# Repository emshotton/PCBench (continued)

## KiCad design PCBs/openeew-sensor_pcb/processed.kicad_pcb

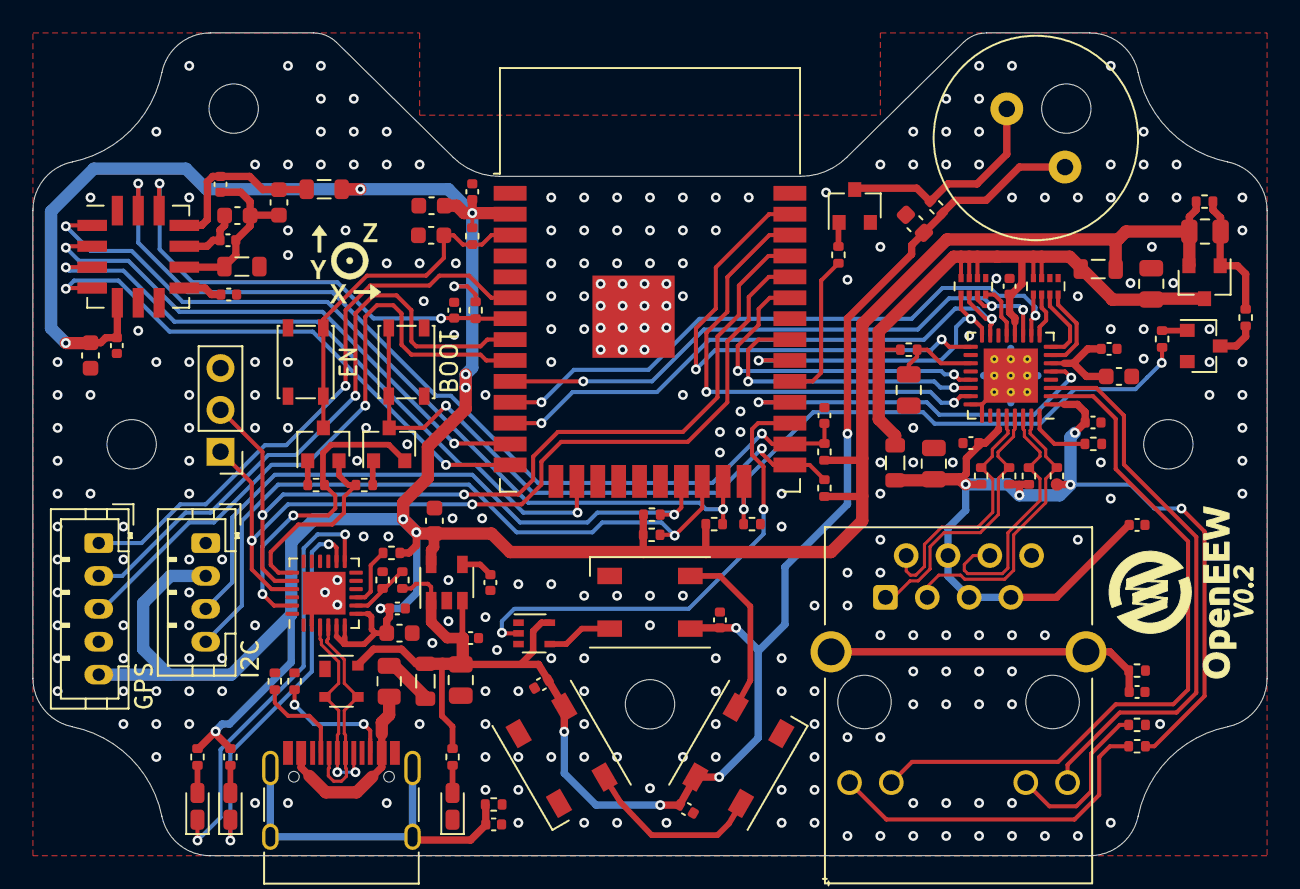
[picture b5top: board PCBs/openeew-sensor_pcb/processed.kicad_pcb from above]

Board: 2 copper layers, 75.0 x 50.0 mm, 101 parts (0 on the bottom side), 79 nets.

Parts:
BZ1: Piezo Buzzer; Buzzer_12.2x6.5mm
C1, C4, C17: 22uF; C_0805_2012Metric
C2, C9: 10uF; C_0805_2012Metric
C3, C13, C18, C30: 1uF; C_0603_1608Metric
C5, C6, C8, C10, C12, C14, C15, C16, C19, C20, C21, C22, C23, C24, C26, C32, C33: 100nF; C_0402_1005Metric
C7, C25, C28: 10uF; C_0603_1608Metric
C11: 2.2uF; C_0603_1608Metric
C27: 4.7uF; C_0603_1608Metric
C29, C31: 4.7nF; C_0402_1005Metric
C34: 470pF; C_0402_1005Metric
D1, D2, D3: WS2812B; LED_WS2812B_PLCC4_5.0x5.0mm_P3.2mm
D4: PRTR5V0U2X; SOT-143
D5, D6, D7: DNP; LED_0603_1608Metric_Castellated
F1: Polyfuse; Fuse_0805_2012Metric
FB1, FB2, FB3: MPZ2012S601ATD25; L_0805_2012Metric
J1: I2C; JST_PH_B4B-PH-K_1x04_P2.00mm_Vertical
J2: HR911105A; RJ45_Hanrun_HR911105A
J3: USB_C_Receptacle_USB2.0; USB_C_Receptacle_HRO_TYPE-C-31-M-12
J4: GPS; JST_PH_B5B-PH-K_1x05_P2.00mm_Vertical
J5: DNP; PinHeader_1x03_P2.54mm_Vertical
L1: DNP; L_0805_2012Metric
L2: MPZ2012S601ATD25; L_0805_2012Metric
Q1, Q3, Q4, Q5: BC817; SOT-23
Q2: WPM2015-3_TR; SOT-23
R1, R3, R5, R6, R12, R15, R23, R24, R25, R27, R29, R30: 10k; R_0402_1005Metric
R2, R13, R31, R32, R101, R102: 1k; R_0402_1005Metric
R7: 12.1k; R_0402_1005Metric
R8, R9, R10, R11: 49.9k; R_0402_1005Metric
R14: 510; R_0402_1005Metric
R16, R17: 5.11k; R_0402_1005Metric
R18: 22.1k; R_0402_1005Metric
R19: 47.5k; R_0402_1005Metric
R20, R21, R26: DNP; R_0402_1005Metric
R22, R28: 1M; R_0402_1005Metric
RN1, RN2: 2.2k; R_Array_Concave_4x0402
SW1, SW2: DNP; SW_SPST_PTS810
U1: ESP32-WROOM-32D; ESP32-WROOM-32
U2: LAN8710A; QFN-32-1EP_5x5mm_P0.5mm_EP3.3x3.3mm_ThermalVias
U3: ADXL355; PLCC-14
U4: MIC5219-3.3YM5; SOT-23-5
U5: 74LVC1G17; SOT-353_SC-70-5
U6: CP2102N-A01-GQFN24; QFN-24-1EP_4x4mm_P0.5mm_EP2.6x2.6mm

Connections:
3.3V_LAN: C4.1, C10.2, L1.2, L2.1, Q2.3, R5.1, RN1.3, RN1.4, RN2.2, RN2.3, RN2.4, U2.12
+3V3: C1.1, C7.2, C8.1, C13.1, C14.1, C25.1, C26.2, C27.2, FB2.2, J1.2, J4.5, L1.1, Q2.2, R1.1, R3.1, R6.1, R12.1, R15.1, R20.1, R21.1, R25.1, R29.1, R31.1, R32.1, U1.2, U3.5, U4.5, U6.5, U6.6, U6.7
+5V: BZ1.1, C2.2, C21.1, C22.1, C23.1, C24.2, C30.1, D1.1, D2.1, D3.1, D4.4, FB1.1, R14.1, R18.2, R26.1, U4.1, U4.3, U5.5
/ACCEL_VSS: C3.2, C5.2, C18.2, C33.2, FB3.2, U3.9
/ACCEL_VSUPPLY: C3.1, C5.1, FB2.1, U3.11
/AG1: J2.9, R102.2
/AY1: J2.12, U2.3
/BOOT: Q5.3, R6.2, SW2.1, U1.25
/BUZZ: R13.2, U1.29
/BZ-: BZ1.2, Q3.3, R14.2
/CC1: J3.A5, R17.1
/CC2: J3.B5, R16.1
/D5_K: D5.2, R20.2
/D6_K: D6.2, R21.2
/EMAC_CLKO_180: U1.28, U2.5
/EMAC_RXD0(RMII): RN2.7, U1.10, U2.11
/EMAC_RXD1(RMII): RN1.5, U1.11, U2.10
/EMAC_RX_CRS_DV: RN2.6, U1.12, U2.15
/EMAC_TXD0(RMII): U1.31, U2.22
/EMAC_TXD1(RMII): U1.36, U2.23
/EMAC_TX_EN(RMII): U1.33, U2.21
/EN: C28.2, Q4.3, R3.2, SW1.2, U1.3
/GPS_PPS: J4.1, U1.6
/GPS_RXD: J4.2, U1.8
/GPS_TXD: J4.3, U1.9
/H_CLK: U1.13, U3.2
/H_CS: R25.2, U1.23, U3.1
/H_MISO: U1.14, U3.4
/H_MOSI: U1.16, U3.3
/I2C_SCL: J1.4, R32.2, U1.22
/I2C_SDA: J1.3, R31.2, U1.21
/INT1: C20.1, R12.2, U1.7, U3.12
/INT2: C32.1, R29.2, U1.26, U3.13
/KG1: J2.10, U2.2
/KY1: J2.11, R101.1
/LAN_VDDCR: C11.2, C12.2, U2.6
/LAN_~RST: C9.2, R5.2, U2.19
/LDO_BYP: C34.1, U4.4
/LED_DAT0: D1.4, U5.4
/LED_DAT1: D1.2, D2.4
/LED_DAT2: D2.2, D3.4
/MDC(RMII): U1.37, U2.17
/MDIO(RMII): RN2.5, U1.30, U2.16
/NEOPIX_DI: U1.27, U5.2
/PHYAD0: RN2.8, U2.13
/PHYAD1: RN1.8, U2.7
/PHYAD2: RN1.7, U2.8
/PHY_PWR: R27.2, R30.2, U1.24
/PWR_LED: D7.2, R26.2
/Q1_C: Q1.3, R2.2
/Q2_G: C1.2, Q2.1, R1.2, R2.1
/Q3_B: Q3.1, R13.1
/Q4_B: Q4.1, R23.2
/Q5_B: Q5.1, R24.2
/RBIAS: R7.1, U2.32
/RJ_SH: C31.2, J2.SH, R28.1
/RMII_SEL: RN1.6, U2.9
/RXD0: J5.1, U1.34, U6.21
/RX_N: J2.6, R11.2, U2.30
/RX_P: J2.3, R10.2, U2.31
/TXD0: J5.2, U1.35, U6.20
/TX_N: J2.2, R9.2, U2.28
/TX_P: J2.1, R8.2, U2.29
/USB_D_N: D4.3, J3.A7, J3.B7, U6.4
/USB_D_P: D4.2, J3.A6, J3.B6, U6.3
/USB_SH: C29.2, J3.S1, R22.1
/V1P8ANA: C18.1, C33.1, U3.10
/V1P8DIG: C19.1, U3.8
/VBUS_C_F: F1.2, J3.A4, J3.A9, J3.B4, J3.B9
/VBUS_DETECT: R18.1, R19.1, U6.8
/VBUS_F_FB: F1.1, FB1.2
/VDD1_2A: C6.1, C15.2, C16.2, C17.2, J2.4, J2.5, J2.7, L2.2, R8.1, R9.1, R10.1, R11.1, R102.1, U2.1, U2.27
/~DTR: Q5.2, R23.1, U6.23
/~RST: R15.2, U6.9
/~RTS: Q4.2, R24.1, U6.19
/~RXT~_LED: D5.1, U6.13
/~TXT~_LED: D6.1, U6.14
GND: C2.1, C4.2, C6.2, C7.1, C8.2, C9.1, C10.1, C11.1, C12.1, C13.2, C14.2, C15.1, C16.1, C17.1, C19.2, C20.2, C21.2, C22.2, C23.2, C24.1, C25.2, C26.1, C27.1, C28.1, C29.1, C30.2, C31.1, C32.2, C34.2, D1.3, D2.3, D3.3, D4.1, D7.1, FB3.1, J1.1, J2.8, J3.A1, J3.A12, J3.B1, J3.B12, J4.4, J5.3, Q1.2, Q3.2, R7.2, R16.2, R17.2, R19.2, R22.2, R28.2, R30.1, R101.2, RN1.1, RN1.2, RN2.1, SW1.1, SW2.2, U1.1, U1.15, U1.38, U1.39, U2.24, U2.25, U2.33, U3.6, U4.2, U5.3, U6.2, U6.25
unnamed: Q1.1, R27.1

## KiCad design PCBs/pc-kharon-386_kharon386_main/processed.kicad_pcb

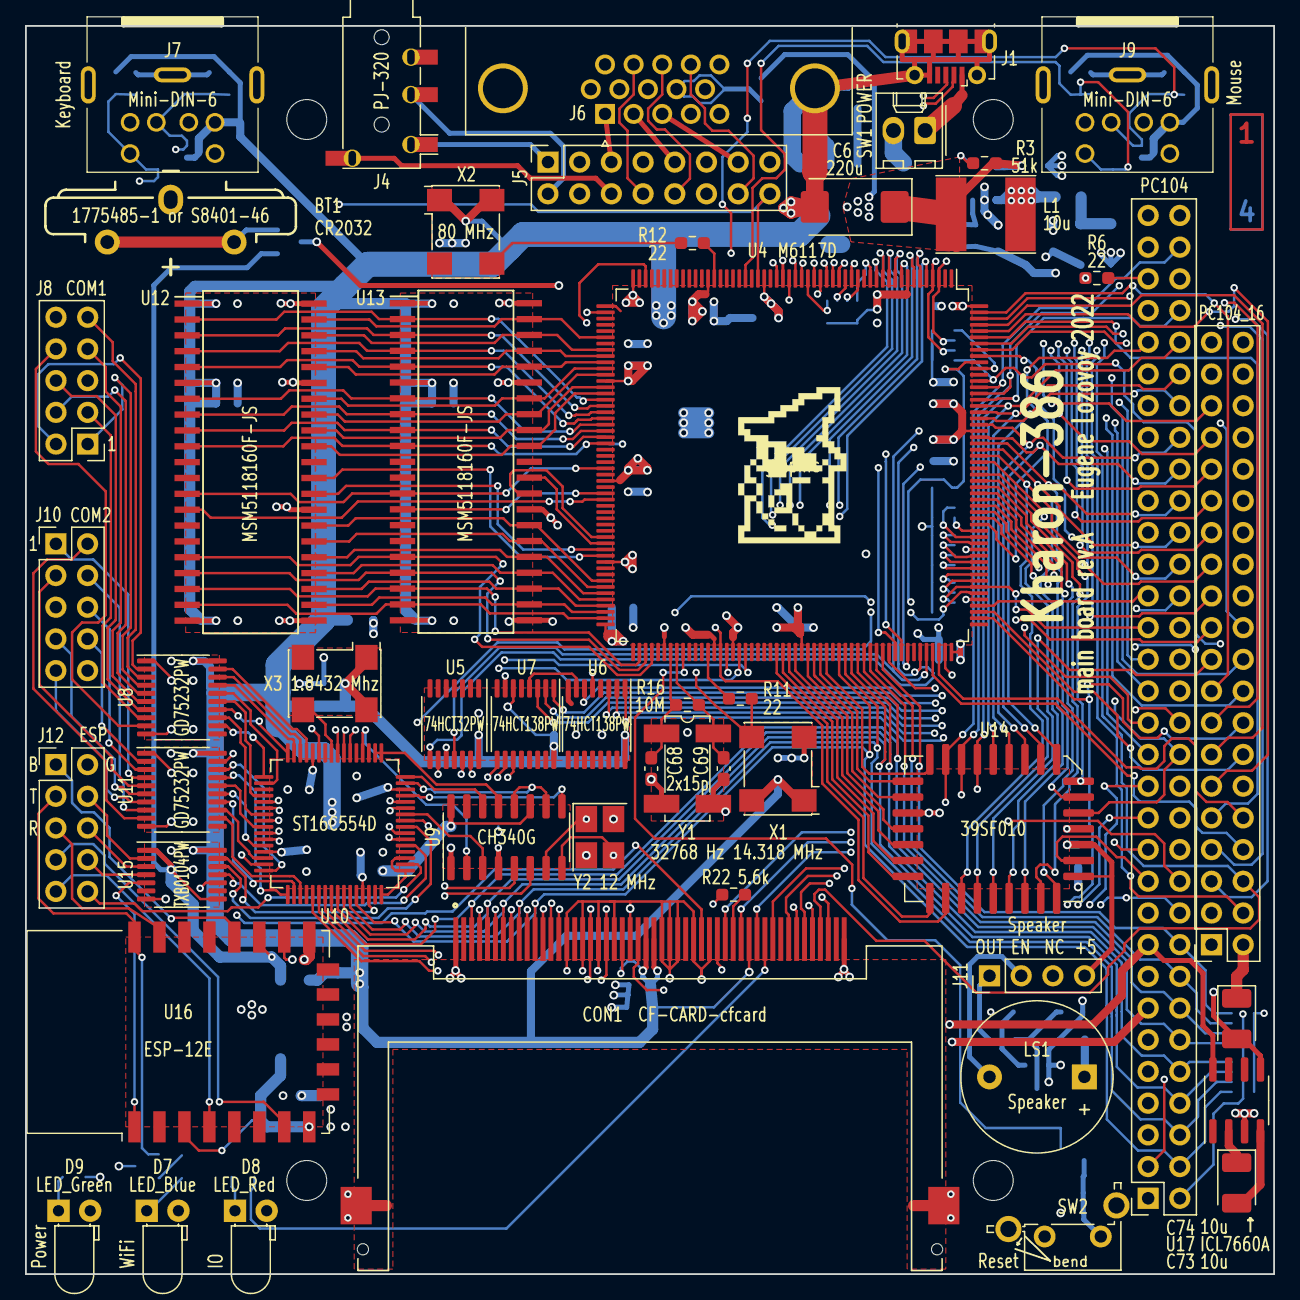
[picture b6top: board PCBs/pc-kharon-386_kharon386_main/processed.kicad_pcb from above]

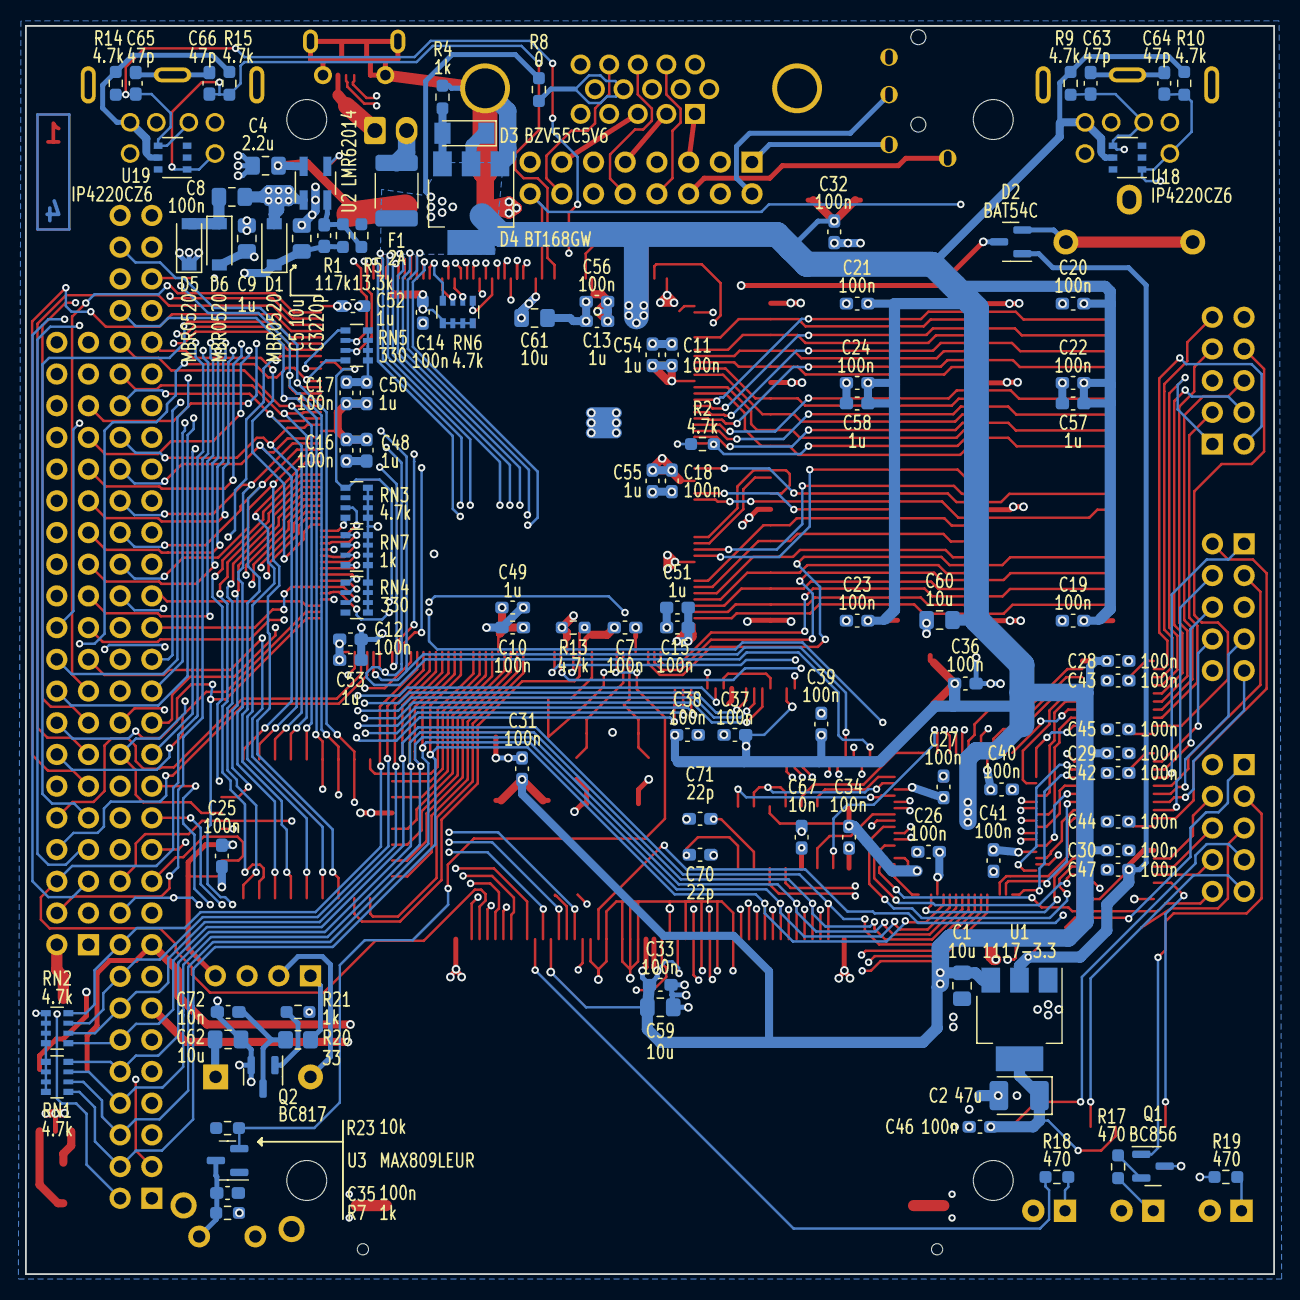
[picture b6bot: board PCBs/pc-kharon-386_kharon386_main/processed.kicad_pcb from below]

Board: 4 copper layers, 100.0 x 100.0 mm, 163 parts (107 on the bottom side), 248 nets.

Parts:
BT1: 1775485-1 or S8401-46; CR2032V
C1, C5, C59, C60, C61, C62: 10u; C_0805_2012Metric_Pad1.18x1.45mm_HandSolder
C2: 47u; CP_EIA-3528-21_Kemet-B_Pad1.50x2.35mm_HandSolder
C3: 220p; C_0603_1608Metric_Pad1.08x0.95mm_HandSolder
C4: 2.2u; C_0805_2012Metric_Pad1.18x1.45mm_HandSolder
C6: 220u; CP_EIA-7343-31_Kemet-D_Pad2.25x2.55mm_HandSolder
C7, C10, C11, C12, C13, C14, C15, C16, C17, C18, C19, C20, C21, C22, C23, C24, C25, C26, C27, C28, C29, C30, C31, C32, C33, C34, C35, C36, C37, C38, C39, C40, C41, C42, C43, C44, C45, C46, C47: 100n; C_0603_1608Metric_Pad1.08x0.95mm_HandSolder
C8: 100n; C_0805_2012Metric_Pad1.18x1.45mm_HandSolder
C9: 1u; C_0805_2012Metric_Pad1.18x1.45mm_HandSolder
C48, C49, C50, C51, C52, C53, C54, C55, C56, C57, C58: 1u; C_0603_1608Metric_Pad1.08x0.95mm_HandSolder
C63, C64, C65, C66: 47p; C_0603_1608Metric_Pad1.08x0.95mm_HandSolder
C67, C72: 10n; C_0603_1608Metric_Pad1.08x0.95mm_HandSolder
C68, C69: 15p; C_0603_1608Metric_Pad1.08x0.95mm_HandSolder
C70, C71: 22p; C_0603_1608Metric_Pad1.08x0.95mm_HandSolder
C73, C74: 10u; CP_EIA-3528-21_Kemet-B_Pad1.50x2.35mm_HandSolder
CON1: CF-CARD-cfcard; TE_1734451-1-LONG
D1, D5, D6: MBR0520; D_SOD-123
D2: BAT54C; SOT-23
D3: BZV55C5V6; D_MiniMELF
D4: BT168GW; SOT-223-3_TabPin2
D7: LED_Blue; LED_D3.0mm_Horizontal_O1.27mm_Z6.0mm
D8: LED_Red; LED_D3.0mm_Horizontal_O1.27mm_Z6.0mm
D9: LED_Green; LED_D3.0mm_Horizontal_O1.27mm_Z6.0mm
F1: 2A; Fuse_1812_4532Metric_Pad1.30x3.40mm_HandSolder
H1, H2, H3, H4: Screw M3 dk=5mm L=4mm; MountingHole_3.2mm_M3_dk5.2mm_Mask
J1: USB_B_Micro; USB_Micro-B_Molex-105017-0001
J2: PC104_16; PinSocket_2x20_P2.54mm_Vertical
J3: PC104; PinSocket_2x32_P2.54mm_Vertical
J4: PJ-320; PJ-320A_D
J5: Conn_02x08_Odd_Even; PinSocket_2x08_P2.54mm_Vertical
J6: DB15_Female_HighDensity_MountingHoles; DSUB-15-HD_Female_Horizontal_P2.29x1.98mm_EdgePinOffset3.03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
J7, J9: Mini-DIN-6; minidin-6
J8: COM1; PinHeader_2x05_P2.54mm_Vertical
J10: COM2; PinHeader_2x05_P2.54mm_Vertical
J11: Conn_01x04; PinHeader_1x04_P2.54mm_Vertical
J12: ESP; PinHeader_2x05_P2.54mm_Vertical
L1: 10u; L_Taiyo-Yuden_NR-60xx_HandSoldering
LOGO1: graphic; black-mage-12.5x8.6
LS1: Speaker; Buzzer_12x9.5RM7.6
Q1: BC856; SOT-23
Q2: BC817; SOT-23
R1: 117k; R_0603_1608Metric_Pad0.98x0.95mm_HandSolder
R2, R9, R10, R13, R14, R15: 4.7k; R_0603_1608Metric_Pad0.98x0.95mm_HandSolder
R3: 51k; R_0603_1608Metric_Pad0.98x0.95mm_HandSolder
R4, R7, R21: 1k; R_0603_1608Metric_Pad0.98x0.95mm_HandSolder
R5: 13.3k; R_0603_1608Metric_Pad0.98x0.95mm_HandSolder
R6, R11, R12: 22; R_0603_1608Metric_Pad0.98x0.95mm_HandSolder
R8: 0; R_0603_1608Metric_Pad0.98x0.95mm_HandSolder
R16: 10M; R_0603_1608Metric_Pad0.98x0.95mm_HandSolder
R17, R18, R19: 470; R_0603_1608Metric_Pad0.98x0.95mm_HandSolder
R20: 33; R_0805_2012Metric_Pad1.20x1.40mm_HandSolder
R22: 5.6k; R_0603_1608Metric_Pad0.98x0.95mm_HandSolder
R23: 10k; R_0603_1608Metric_Pad0.98x0.95mm_HandSolder
RN1, RN2, RN3, RN6: 4.7k; R_Array_Convex_4x0603
RN4, RN5: 330; R_Array_Convex_4x0603
RN7: 1k; R_Array_Convex_4x0603
SW1: Jumper / Pin header 1x2 Pitch=2.54mm; Molex_KK-254_AE-6410-02A_1x02_P2.54mm_Vertical
SW2: SW_Push; SW_Tactile_SPST_Angled_PTS645Vx83-2LFS
U1: 1117-3.3; SOT-223-3_TabPin2
U2: LMR62014; SOT-23-5_HandSoldering
U3: MAX809LEUR; SOT-23
U4: M6117D; PQFP-208_28x28mm_P0.5mm
U5: 74HCT32PW; TSSOP-14_4.4x5mm_P0.65mm
U6, U7: 74HCT138PW; TSSOP-16_4.4x5mm_P0.65mm
U8, U11: GD75232PW; TSSOP-20_4.4x6.5mm_P0.65mm
U9: CH340G; SOIC-16_3.9x9.9mm_P1.27mm
U10: ST16C554D; LQFP-64_10x10mm_P0.5mm
U12, U13: MSM5118160F-JS; SOJ-42
U14: 39SF010; PLCC-32_11.4x14.0mm_P1.27mm-longpads
U15: TXB0104PW; TSSOP-14_4.4x5mm_P0.65mm
U16: ESP-12E
U17: ICL7660A; SOIC-8_3.9x4.9mm_P1.27mm
U18, U19: IP4220CZ6; TSOP-6_1.65x3.05mm_P0.95mm
X1: 14.318 MHz; Oscillator_SMD_7050_7.0x5.0mm
X2: 80 MHz; Oscillator_SMD_7050_7.0x5.0mm
X3: 1.8432 Mhz; Oscillator_SMD_7050_7.0x5.0mm
Y1: 32768 Hz; Crystal_SMD_SeikoEpson_MC306-4Pin_8.0x3.2mm_HandSoldering
Y2: 12 MHz; Crystal_SMD_SeikoEpson_TSX3225-4Pin_3.2x2.5mm_HandSoldering

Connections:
+3V3: C2.1, C46.2, C47.2, D2.1, U1.2 (VO), U15.1 (VCCA), U15.8 (OE), U16.3 (EN), U16.8 (VCC), U16.17 (GPIO2)
+5V: C1.2, C4.2, C6.1, C10.2, C11.2, C12.2, C13.2, C14.2, C15.2, C16.2, C17.2, C18.2, C19.2, C20.2, C21.2, C22.2, C23.2, C24.2, C25.2, C26.2, C27.2, C28.2, C29.2, C30.2, C31.2, C32.2, C33.2, C34.1, C36.1, C37.1, C38.1, C39.1, C40.1, C41.1, C48.2, C49.2, C50.2, C51.2, C52.2, C53.2, C54.1, C55.1, C56.1, C57.1, C58.1, C59.1, C60.1, C61.1, C62.1, CON1.13 (VCC2), CON1.36 (~WE), CON1.38 (VCC1), CON1.44 (~REG), D3.1 (K), D4.2 (A), D7.2 (A), D8.2 (A), D9.2 (A), F1.1, J2.34, J3.5, J3.57, J7.4, J9.4, J11.4, L1.1, LS1.1, R2.1, R3.1, R7.1, R8.1, R9.1, R10.1, R14.1, R15.1, RN1.5 (R4.2), RN1.6 (R3.2), RN1.7 (R2.2), RN1.8 (R1.2), RN2.5 (R4.2), RN2.6 (R3.2), RN2.7 (R2.2), RN2.8 (R1.2), RN3.5 (R4.2), RN3.6 (R3.2), RN3.7 (R2.2), RN3.8 (R1.2), RN4.5 (R4.2), RN4.6 (R3.2), RN4.7 (R2.2), RN4.8 (R1.2), RN5.5 (R4.2), RN5.6 (R3.2), RN5.7 (R2.2), RN5.8 (R1.2), RN7.5 (R4.2), RN7.6 (R3.2), RN7.7 (R2.2), RN7.8 (R1.2), U1.3 (VI), U2.5 (Vin), U4.1 (VCC1), U4.15 (VCC2), U4.38 (VCC3), U4.46 (VCC4), U4.53 (VCC5), U4.59 (VCC6), U4.76 (VCC7), U4.85 (VCC8), U4.105 (VCC9), U4.125 (VCC11), U4.137 (VCC12), U4.150 (VCC13), U4.157 (VCC14), U4.182 (VCC15), U4.197 (VCC16), U5.14 (VCC), U6.16 (VCC), U7.6 (E3), U7.16 (VCC), U8.20 (VCC), U9.11 (~RI), U9.16 (VCC), U10.4 (VCC), U10.19 (RIB#), U10.21 (VCC), U10.35 (VCC), U10.52 (VCC), U10.63 (RIA#), U11.20 (VCC), U12.1 (VCC), U12.6 (VCC), U12.21 (VCC), U13.1 (VCC), U13.6 (VCC), U13.21 (VCC), U14.1 (A18), U14.30 (A17), U14.32 (VCC), U15.14 (VCCB), U18.5 (+), U19.5 (+), X1.1 (EN), X1.4 (V+), X2.1 (EN), X2.4 (V+), X3.1 (EN), X3.4 (V+)
+12V: C3.1, C5.2, C42.2, C43.2, D1.1 (K), J3.17, R1.1, U8.1 (VDD), U11.1 (VDD), U17.8 (V+)
+BATT: C7.1, D2.3, U4.110 (VBAT)
-12V: C9.1, C44.2, C45.2, C74.2, D6.2 (A), J3.13, U8.10 (VSS), U11.10 (VSS), U17.5 (VOUT)
/0x2E8: U7.11 (O4), U10.7 (CSA#)
/0x2F8: U7.9 (O6), U10.42 (CSD#)
/0x3E8: U7.10 (O5), U10.11 (CSB#)
/0x3F8: U7.7 (O7), U10.38 (CSC#)
/14MHz: R6.2, R11.2, X1.3 (OUT)
/AEN: J3.22, RN3.1 (R1.1), U4.199 (AEN), U6.5 (E2)
/BALE: J3.55, U4.173 (BALE)
/BD0: R2.2, U4.75 (BD0), U12.10 (DQ7), U13.10 (DQ7)
/BD1: U4.74 (BD1), U12.9 (DQ6), U13.9 (DQ6)
/BD2: U4.73 (BD2), U12.8 (DQ5), U13.8 (DQ5)
/BD3: U4.72 (BD3), U12.7 (DQ4), U13.7 (DQ4)
/BD4: U4.71 (BD4), U12.5 (DQ3), U13.5 (DQ3)
/BD5: U4.70 (BD5), U12.4 (DQ2), U13.4 (DQ2)
/BD6: U4.69 (BD6), U12.3 (DQ1), U13.3 (DQ1)
/BD7: U4.68 (BD7), U12.2 (DQ0), U13.2 (DQ0)
/BD8: U4.67 (BD8), U12.33 (DQ8), U13.33 (DQ8)
/BD9: U4.66 (BD9), U12.34 (DQ9), U13.34 (DQ9)
/BD10: U4.64 (BD10), U12.35 (DQ10), U13.35 (DQ10)
/BD11: U4.63 (BD11), U12.36 (DQ11), U13.36 (DQ11)
/BD12: U4.62 (BD12), U12.38 (DQ12), U13.38 (DQ12)
/BD13: U4.61 (BD13), U12.39 (DQ13), U13.39 (DQ13)
/BD14: U4.60 (BD14), U12.40 (DQ14), U13.40 (DQ14)
/BD15: U4.58 (BD15), U12.41 (DQ15), U13.41 (DQ15)
/CAS0J0: U4.93 (CAS0LJ), U12.31 (~LCAS)
/CAS0J1: U4.92 (CAS0HJ), U12.30 (~UCAS)
/CAS1J0: U4.91 (CAS1LJ), U13.31 (~LCAS)
/CAS1J1: U4.90 (CAS1HJ), U13.30 (~UCAS)
/CD_COM1: U8.17 (RY3), U10.31 (CDC#)
/CD_COM2: U10.49 (CDD#), U11.17 (RY3)
/CLK2: R12.2, X2.3 (OUT)
/CTS1: J8.8, U8.9 (RA5)
/CTS2: J10.8, U11.2 (RA1)
/CTS_COM1: U8.12 (RY5), U10.33 (CTSC#)
/CTS_COM2: U10.47 (CTSD#), U11.19 (RY1)
/CTS_ESP: J12.10, U10.2 (CTSA#)
/CTS_USB: U9.14 (~RTS), U10.16 (CTSB#)
/DACK0: J2.18, RN6.7 (R2.2), U4.16 (DACK0J)
/DACK1: J3.33, RN6.6 (R3.2), U4.18 (DACK1J)
/DACK2: J3.51, U4.20 (DACK2J)
/DACK3: J3.29, U4.22 (DACK3J)
/DACK5: J2.22, RN6.5 (R4.2), U4.24 (DACK5J)
/DACK6: J2.26, U4.26 (DACK6J)
/DACK7: J2.30, U4.28 (DACK7J)
/DCD1: J8.1, U8.4 (RA3)
/DCD2: J10.1, U11.4 (RA3)
/DRQ0: J2.20, U4.17 (DRQ0)
/DRQ1: J3.35, U4.19 (DRQ1)
/DRQ2: J3.11, U4.21 (DRQ2)
/DRQ3: J3.31, U4.23 (DRQ3)
/DRQ5: J2.24, U4.25 (DRQ5)
/DRQ6: J2.28, U4.27 (DRQ6)
/DRQ7: J2.32, U4.29 (DRQ7)
/DSR1: J8.6, U8.7 (RA4)
/DSR2: J10.6, U11.3 (RA2)
/DSR_COM1: U8.14 (RY4), U10.32 (DSRC#)
/DSR_COM2: U10.48 (DSRD#), U11.18 (RY2)
/DSR_USB: U9.13 (~DTR), U10.17 (DSRB#), U10.18 (CDB#)
/DTR1: J8.4, U8.5 (DY1)
/DTR2: J10.4, U11.8 (DY3)
/DTR_COM1: U8.16 (DA1), U10.34 (DTRC#)
/DTR_COM2: U10.46 (DTRD#), U11.13 (DA3)
/DTR_USB: U9.10 (~DSR), U9.12 (~DCD), U10.15 (DTRB#)
/ESP_BOOT: J12.1, U16.18 (GPIO0)
/ESP_CTS: J12.7, U16.7 (GPIO13)
/ESP_RST: U15.5 (A4), U16.1 (~RST)
/ESP_RTS: J12.9, U16.4 (GPIO16)
/ESP_RX: J12.5, U16.21 (GPIO3/RXD)
/ESP_TX: J12.3, Q1.1 (B), U16.22 (GPIO1/TXD)
/HDCS0: CON1.7 (~CS0), U4.50 (HDCS0J)
/HDCS1: CON1.32 (~CS1), U4.54 (HDCS1J)
/IOCHK: J3.2, RN5.4 (R4.1), U4.196 (IOCHKJ)
/IOCHRDY: CON1.42 (IORDY), J3.20, RN4.2 (R2.1), U4.164 (IOCHRDY)
/IOCS16: CON1.24 (~IOCS16), J2.6, RN5.2 (R2.1), U4.3 (IO16J)
/IOR: CON1.34 (~IORD), J3.27, RN7.4 (R4.1), U4.166 (IORJ), U10.40 (IOR#)
/IOW: CON1.35 (~IOWR), J3.25, RN7.3 (R3.1), U4.167 (IOWJ), U10.9 (IOW#)
/IRQ3: J3.49, U4.152 (IRQ3), U5.11
/IRQ4: J3.47, U4.151 (IRQ4), U5.8
/IRQ5: J3.45, U4.149 (IRQ5)
/IRQ6: J3.43, U4.148 (IRQ6)
/IRQ7: J3.41, U4.147 (IRQ7)
/IRQ9: J3.7, U4.146 (IRQ9)
/IRQ10: J2.8, U4.153 (IRQ10)
/IRQ11: J2.10, U4.154 (IRQ11)
/IRQ14: CON1.37 (INTRQ), J2.16, U4.158 (IRQ14)
/IRQ15: J2.14, U4.159 (IRQ15)
/KBCLK: C64.1, J7.5, R10.2, U4.122 (KBCLK), U18.1
/KBDAT: C63.1, J7.1, R9.2, U4.123 (KBDATA), U18.4
/KBSJ: R13.2, U4.119 (ROMKBCSJ), U14.22 (~CE)
/LA17: J2.17, U4.207 (LA17)
/LA18: J2.15, U4.206 (LA18)
/LA19: J2.13, U4.205 (LA19)
/LA20: J2.11, U4.204 (LA20)
/LA21: J2.9, U4.203 (LA21)
/LA22: J2.7, U4.202 (LA22)
/LA23: J2.5, U4.201 (LA23)
/MA0: U4.108 (MA0), U12.17 (MA0), U13.17 (MA0)
/MA1: U4.107 (MA1), U12.18 (MA1), U13.18 (MA1)
/MA2: U4.106 (MA2), U12.19 (MA2), U13.19 (MA2)
/MA3: U4.103 (MA3), U12.20 (MA3), U13.20 (MA3)
/MA4: U4.102 (MA4), U12.23 (MA4), U13.23 (MA4)
/MA5: U4.101 (MA5), U12.24 (MA5), U13.24 (MA5)
/MA6: U4.100 (MA6), U12.25 (MA6), U13.25 (MA6)
/MA7: U4.99 (MA7), U12.26 (MA7), U13.26 (MA7)
/MA8: U4.98 (MA8), U12.27 (MA8), U13.27 (MA8)
/MA9: U4.97 (MA9), U12.28 (MA9), U13.28 (MA9)
/MASTER: J2.36, RN5.1 (R1.1), U4.198 (MASTERJ)
/MEMCS16: J2.4, RN5.3 (R3.1), U4.4 (MEM16J)
/MEMR: J2.19, RN3.3 (R3.1), U4.171 (MRDJ), U14.24 (~OE)
/MEMW: J2.21, RN3.4 (R4.1), U4.172 (MWTJ)
/MSCLK: C66.1, J9.5, R15.2, U4.34 (MSCLK), U19.1
/MSDAT: C65.1, J9.1, R14.2, U4.155 (IRQ12/MSDATA), U19.4
/NOWS: J3.15, RN4.1 (R1.1), U4.165 (NOWSJ)
/PWG: R23.1, U3.2 (~RST), U4.113 (PWG)
/RASJ0: U4.84 (RAS0J), U12.14 (~RAS)
/RASJ1: U4.83 (RAS1J), U13.14 (~RAS)
/REFRESH: J3.37, RN4.3 (R3.1), U4.163 (REFRESHJ)
/RESETL: CON1.41 (~RESET), U4.120 (RESETLJ), U15.10 (B4)
/RI1: J8.9, U8.3 (RA2)
/RI2: J10.9, U11.7 (RA4)
/RI_COM1: U8.18 (RY2), U10.30 (RIC#)
/RI_COM2: U10.50 (RID#), U11.14 (RY4)
/RSTDRV: J3.3, U4.162 (RSTDRV), U10.27 (RESET)
/RTS1: J8.7, U8.6 (DY2)
/RTS2: J10.7, U11.6 (DY2)
/RTS_COM1: U8.15 (DA2), U10.36 (RTSC#)
/RTS_COM2: U10.44 (RTSD#), U11.15 (DA2)
/RTS_ESP: U10.5 (RTSA#), U15.11 (B3)
/RTS_USB: U9.9 (~CTS), U10.13 (RTSB#)
/RX1: J8.2, U8.2 (RA1)
/RX2: J10.2, U11.9 (RA5)
/RX_COM1: U8.19 (RY1), U10.29 (RXC)
/RX_COM2: U10.51 (RXD), U11.12 (RY5)
/RX_ESP: U10.62 (RXA), U15.13 (B1)
/RX_USB: U9.2 (TXD), U10.20 (RXB)
/SA0: CON1.20 (A0), J3.62, U4.195 (SA0), U10.24 (A0), U14.12 (A0)
/SA1: CON1.19 (A1), J3.60, U4.194 (SA1), U10.23 (A1), U14.11 (A1)
/SA2: CON1.18 (A2), J3.58, U4.193 (SA2), U10.22 (A2), U14.10 (A2)
/SA3: J3.56, U4.192 (SA3), U7.3 (A2), U14.9 (A3)
/SA4: J3.54, U4.191 (SA4), U7.2 (A1), U14.8 (A4)
/SA5: J3.52, U4.190 (SA5), U6.6 (E3), U14.7 (A5)
/SA6: J3.50, U4.189 (SA6), U6.1 (A0), U14.6 (A6)
/SA7: J3.48, U4.187 (SA7), U6.2 (A1), U14.5 (A7)
/SA8: J3.46, U4.186 (SA8), U7.1 (A0), U14.27 (A8)
/SA9: J3.44, U4.185 (SA9), U6.3 (A2), U14.26 (A9)
/SA10: J3.42, U4.184 (SA10), U14.23 (A10)
/SA11: J3.40, U4.183 (SA11), U14.25 (A11)
/SA12: J3.38, U4.181 (SA12), U14.4 (A12)
/SA13: J3.36, U4.180 (SA13), U14.28 (A13)
/SA14: J3.34, U4.179 (SA14), U14.29 (A14)
/SA15: J3.32, U4.178 (SA15), U14.3 (A15)
/SA16: J3.30, U4.177 (SA16), U14.2 (A16)
/SA17: J3.28, U4.176 (SA17)
/SA18: J3.26, U4.175 (SA18)
/SA19: J3.24, U4.174 (SA19)
/SBHE: J2.3, U4.200 (BHEJ)
/SD0: CON1.21 (D0), J3.18, RN2.4 (R4.1), U4.145 (SD0), U10.53 (D0)
/SD1: CON1.22 (D1), J3.16, RN2.3 (R3.1), U4.144 (SD1), U10.54 (D1)
/SD2: CON1.23 (D2), J3.14, RN2.2 (R2.1), U4.143 (SD2), U10.55 (D2)
/SD3: CON1.2 (D3), J3.12, RN2.1 (R1.1), U4.142 (SD3), U10.56 (D3)
/SD4: CON1.3 (D4), J3.10, RN1.4 (R4.1), U4.141 (SD4), U10.57 (D4)
/SD5: CON1.4 (D5), J3.8, RN1.3 (R3.1), U4.140 (SD5), U10.58 (D5)
/SD6: CON1.5 (D6), J3.6, RN1.2 (R2.1), U4.139 (SD6), U10.59 (D6)
/SD7: CON1.6 (D7), J3.4, RN1.1 (R1.1), U4.138 (SD7), U10.60 (D7)
/SD8: CON1.47 (D8), J2.23, U4.5 (SD8)
/SD9: CON1.48 (D9), J2.25, U4.6 (SD9)
/SD10: CON1.49 (D10), J2.27, U4.7 (SD10)
/SD11: CON1.27 (D11), J2.29, U4.9 (SD11)
/SD12: CON1.28 (D12), J2.31, U4.10 (SD12)
/SD13: CON1.29 (D13), J2.33, U4.11 (SD13)
/SD14: CON1.30 (D14), J2.35, U4.12 (SD14)
/SD15: CON1.31 (D15), J2.37, U4.13 (SD15)
/SMEMR: J3.23, RN7.2 (R2.1), U4.168 (SMEMRJ)
/SMEMW: J3.21, RN7.1 (R1.1), U4.170 (SMEMWJ), U14.31 (~WE)
/SND_L: J4.T, J5.1
/SND_R: J4.R1, J5.2
/SPKR: J5.16, R21.1, U4.32 (SPKR)
/SYSCLK: J3.39, U4.160 (ATCLK)
/TC: J3.53, RN6.8 (R1.2), U4.14 (TC)
/TX1: J8.3, U8.8 (DY3)
/TX2: J10.3, U11.5 (DY1)
/TX_COM1: U8.13 (DA3), U10.39 (TXC)
/TX_COM2: U10.41 (TXD), U11.16 (DA1)
/TX_ESP: U10.8 (TXA), U15.12 (B2)
/TX_USB: U9.3 (RXD), U10.10 (TXB)
/UART_INTA: U5.9, U10.6 (INTA)
/UART_INTB: U5.12, U10.12 (INTB)
/UART_INTC: U5.10, U10.37 (INTC)
/UART_INTD: U5.13, U10.43 (INTD)
/USB_DN: J1.2 (D-), U9.6 (UD-)
/USB_DP: J1.3 (D+), U9.5 (UD+)
/VGA_B: J5.13, J6.3
/VGA_G: J5.9, J6.2
/VGA_HS: J5.10, J6.13
/VGA_MON: J5.8, J6.12
/VGA_R: J5.5, J6.1
/VGA_VS: J5.14, J6.14
/WEJ: U4.79 (WEJ), U12.13 (~W), U13.13 (~W)
/XD0: U4.136 (XD0), U14.13 (D0)
/XD1: U4.135 (XD1), U14.14 (D1)
/XD2: U4.134 (XD2), U14.15 (D2)
/XD3: U4.133 (XD3), U14.17 (D3)
/XD4: U4.131 (XD4), U14.18 (D4)
/XD5: U4.130 (XD5), U14.19 (D5)
/XD6: U4.129 (XD6), U14.20 (D6)
/XD7: U4.128 (XD7), U14.21 (D7)
/~CF_BUSY: CON1.45 (~DASP), R18.2
GND: BT1.2 (-), C1.1, C2.2, C4.1, C5.1, C6.2, C7.2, C9.2, C10.1, C11.1, C12.1, C13.1, C14.1, C15.1, C16.1, C17.1, C18.1, C19.1, C20.1, C21.1, C22.1, C23.1, C24.1, C25.1, C26.1, C27.1, C28.1, C29.1, C30.1, C31.1, C32.1, C33.1, C34.2, C35.2, C36.2, C37.2, C38.2, C39.2, C40.2, C41.2, C42.1, C43.1, C44.1, C45.1, C46.1, C47.1, C48.1, C49.1, C50.1, C51.1, C52.1, C53.1, C54.2, C55.2, C56.2, C57.2, C58.2, C59.2, C60.2, C61.2, C62.2, C63.2, C64.2, C65.2, C66.2, C67.1, C68.2, C69.2, C70.2, C71.2, C72.2, C74.1, CON1.1 (GND1), CON1.8 (A10), CON1.9 (~ATASEL), CON1.10 (A9), CON1.11 (A8), CON1.12 (A7), CON1.14 (A6), CON1.15 (A5), CON1.16 (A4), CON1.17 (A3), CON1.39 (~CSEL), CON1.50 (GND2), CON1.S1 (Shield), CON1.S2 (Shield), D4.1 (K), D5.1 (K), J1.5 (GND), J1.6 (Shield), J2.1, J2.2, J2.38, J2.40, J3.1, J3.61, J3.63, J3.64, J4.R2, J5.3, J5.4, J5.7, J5.11, J5.12, J6.0, J6.5, J6.6, J6.7, J6.8, J6.10, J7.0, J7.3, J8.5, J9.0, J9.3, J10.5, J12.2, Q1.3 (C), Q2.2 (E), R4.2, R5.1, R13.1, R19.2, R22.2, R23.2, RN6.1 (R1.1), RN6.2 (R2.1), RN6.3 (R3.1), RN6.4 (R4.1), SW2.2, U1.1 (GND), U2.2 (GND), U3.1 (GND), U4.8 (GND1), U4.31 (GND2), U4.40 (GND3), U4.52 (GND4), U4.65 (GND5), U4.81 (GND6), U4.94 (GND7), U4.104 (GND8), U4.118 (GND9), U4.121 (GND10), U4.132 (GND11), U4.156 (GND12), U4.161 (GND13), U4.169 (GND14), U4.188 (GND15), U4.208 (GND16), U5.1, U5.2, U5.4, U5.5, U5.7 (GND), U6.4 (E1), U6.8 (GND), U7.5 (E2), U7.8 (GND), U8.11 (GND), U9.1 (GND), U10.14 (GND), U10.28 (GND), U10.45 (GND), U10.61 (GND), U11.11 (GND), U12.22 (GND), U12.29 (~OE), U12.37 (GND), U12.42 (GND), U13.22 (GND), U13.29 (~OE), U13.37 (GND), U13.42 (GND), U14.16 (GND), U15.7 (GND), U16.15 (GND), U16.16 (GPIO15), U17.3 (GND), U18.2 (-), U19.2 (-), X1.2 (GND), X2.2 (GND), X3.2 (GND), Y1.2, Y1.3, Y2.2, Y2.4
unnamed: BT1.1 (+), D2.2
unnamed: C3.2, R1.2, R5.2, U2.3 (FB)
unnamed: C8.1, D1.2 (A), L1.2, U2.1 (SW)
unnamed: C8.2, D5.2 (A), D6.1 (K)
unnamed: C35.1, R7.2, SW2.1, U3.3 (VCC)
unnamed: C67.2, U9.4 (V3)
unnamed: C68.1, R16.1, U4.111 (XTAL1), Y1.1
unnamed: C69.1, R16.2, U4.112 (XTAL2), Y1.4
unnamed: C70.1, U9.8 (XO), Y2.3
unnamed: C71.1, U9.7 (XI), Y2.1
unnamed: C72.1, Q2.3 (C), R20.2
unnamed: C73.1, U17.2 (CAP+)
unnamed: C73.2, U17.4 (CAP-)
unnamed: CON1.43 (~INPACK), R22.1
unnamed: D3.2 (A), D4.3 (G), R4.1
unnamed: D7.1 (K), R17.1
unnamed: D8.1 (K), R18.1
unnamed: D9.1 (K), R19.1
unnamed: F1.2, SW1.2 (B)
unnamed: J1.1 (VBUS), SW1.1 (A)
unnamed: J3.59, R6.1
unnamed: J4.S, J5.6
unnamed: J6.9, R8.2
unnamed: J11.1, R20.1
unnamed: J11.2, LS1.2
unnamed: J12.4, U15.2 (A1)
unnamed: J12.6, U15.3 (A2)
unnamed: J12.8, U15.4 (A3)
unnamed: Q1.2 (E), R17.2
unnamed: Q2.1 (B), R21.2
unnamed: R3.2, U2.4 (~SHDN)
unnamed: R11.1, U4.117 (OSC14M)
unnamed: R12.1, U4.39 (BCLK2)
unnamed: U6.7 (O7), U7.4 (E1)
unnamed: U10.1 (DSRA#), U10.3 (DTRA#), U10.64 (CDA#)
unnamed: U10.25 (XTAL1), X3.3 (OUT)
